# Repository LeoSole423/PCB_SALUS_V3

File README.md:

# PCB SALUS V3

PCB de control para el robot Ackermann SALUS. Esta revision se inspira en la
arquitectura de `Hoja-Base`, pero usa un ESP32-S3 y se mantiene como un diseno
independiente.

## Abrir el proyecto

En KiCad 10, abre `PCB_SALUS_v3.kicad_pro`. El esquema raiz contiene tres
hojas jerarquicas activas: `ESP32`, `SENSORES` y `ALIMENTACION`.

El diseño actual corresponde a `fabricacion/actual/JLCPCB_2026-10-15_SALUS_v3_D9_DNP/`.
Incluye cuatro agujeros M3 NPTH, contorno redondeado y R4 de 120 ohm montada
como terminacion RS-485. El sufijo R4 identifica esa resistencia. Las fuentes
en `origen/` coinciden con los archivos de trabajo al registrar este paquete.

Los informes archivados del 20 de agosto registran cero conexiones sin rutear
y cero errores DRC/ERC, con avisos e ignorados documentados. Esto no sustituye
la validacion electrica ni las pruebas de banco. Antes de pedir, seguir
`README-pedido.txt` y revisar el montaje en el visor JLCPCB.

`JLCPCB_2026-08-20_SALUS_v3/` conserva la exportacion anterior del mismo dia,
sin R4 montada; los paquetes de julio y del 12 de agosto son historicos.

## Organización

- [Mapa del repositorio](docs/09_ORGANIZACION_REPOSITORIO.md).
- [Índice de fabricación](fabricacion/README.md): entrega actual, históricas y cotizaciones.
- [Archivo histórico](archivo/README.md): respaldos, v2 y exportaciones antiguas.
- `referencias/jlcpcb/`: plantillas XLSX del proveedor.

## Arquitectura actual

- `U8`: ESP32-S3-WROOM-1-N8R2.
- `U1`: LDO AMS1117CD-3.3; J5 alimenta `5V_SYS` mediante D7; D9 se conserva como DNP y USB J16 no alimenta la lógica.
- `JP1` cerrado alimenta `+3.3V` desde el LDO; `JP2` abierto permite una
  fuente alternativa por J20 con selección de puentes apropiada.
- J16 es USB nativo; J1 es debug UART0, J3/J21 son RS-485 mediante U2.
- BMI088, I2C, interfaz BTS7960, siete salidas de relé, Hall, finales,
  acelerador y PPM. Receptor RC previsto: FlySky FS-iA6B.
- J19 recibe 7 V externos para J17/J18; no hay conversión de potencia de tracción.

La [revisión completa del 15/10/2026](docs/reviews/2026-10-15/REVISION_COMPLETA.md)
registra los límites actuales: no hay aprobación incondicional para fabricar
ni integrar. Resolver especialmente el rango del LM358, alimentación e interfaces.
La documentación histórica que menciona U9 buck o U3 CP2102N describe etapas anteriores.

## Documentacion

- [Contexto del proyecto](docs/00_CONTEXTO_PROYECTO.md)
- [Estructura del esquematico y librerias](docs/01_ESTRUCTURA_ESQUEMATICO_Y_LIBRERIAS.md)
- [Validacion y pruebas](docs/02_VALIDACION_Y_PRUEBAS.md)
- [Revision BOM y huellas JLCPCB](docs/03_REVISION_BOM_JLCPCB.md)
- [Puente H BTS7960](docs/04_PUENTE_H_BTS7960.md)
- [Mapa de submodulos y pinout](docs/05_MAPA_DE_SUBMODULOS_Y_PINOUT.md)
- [Revision V3](docs/06_REVISION_V3_2026-07-15.md)
- [Generacion CPL auditable KiCad → JLCPCB](docs/07_CPL_AUDITABLE_KICAD_JLCPCB.md)
- [Validacion del filtro PWM del acelerador](docs/08_VALIDACION_FILTRO_ACELERADOR_PWM.md)

## CPL para JLCPCB

Para toda exportación futura de montaje usar exclusivamente
`tools/jlc_cpl.py` y el perfil versionado `config/jlcpcb-cpl.json`. La guía
incluye el flujo reproducible para agentes, auditoría de centroides y
calibración desde el visor de JLCPCB. No editar rotaciones o posiciones
directamente en un CSV.

## Decisiones de integración

El [registro del 15/10/2026](docs/reviews/2026-10-15/DECISIONES_Y_PENDIENTES.md) distingue decisiones y cambios pendientes: conservar el lineal de 3.3 V, USB Serial/JTAG para la Jetson y no añadir detección VBUS. D9 ya está marcado DNP en esquema y PCB y excluido del montaje de la entrega actual. Sus pads/pistas permanecen; no montar ni puentear D9.

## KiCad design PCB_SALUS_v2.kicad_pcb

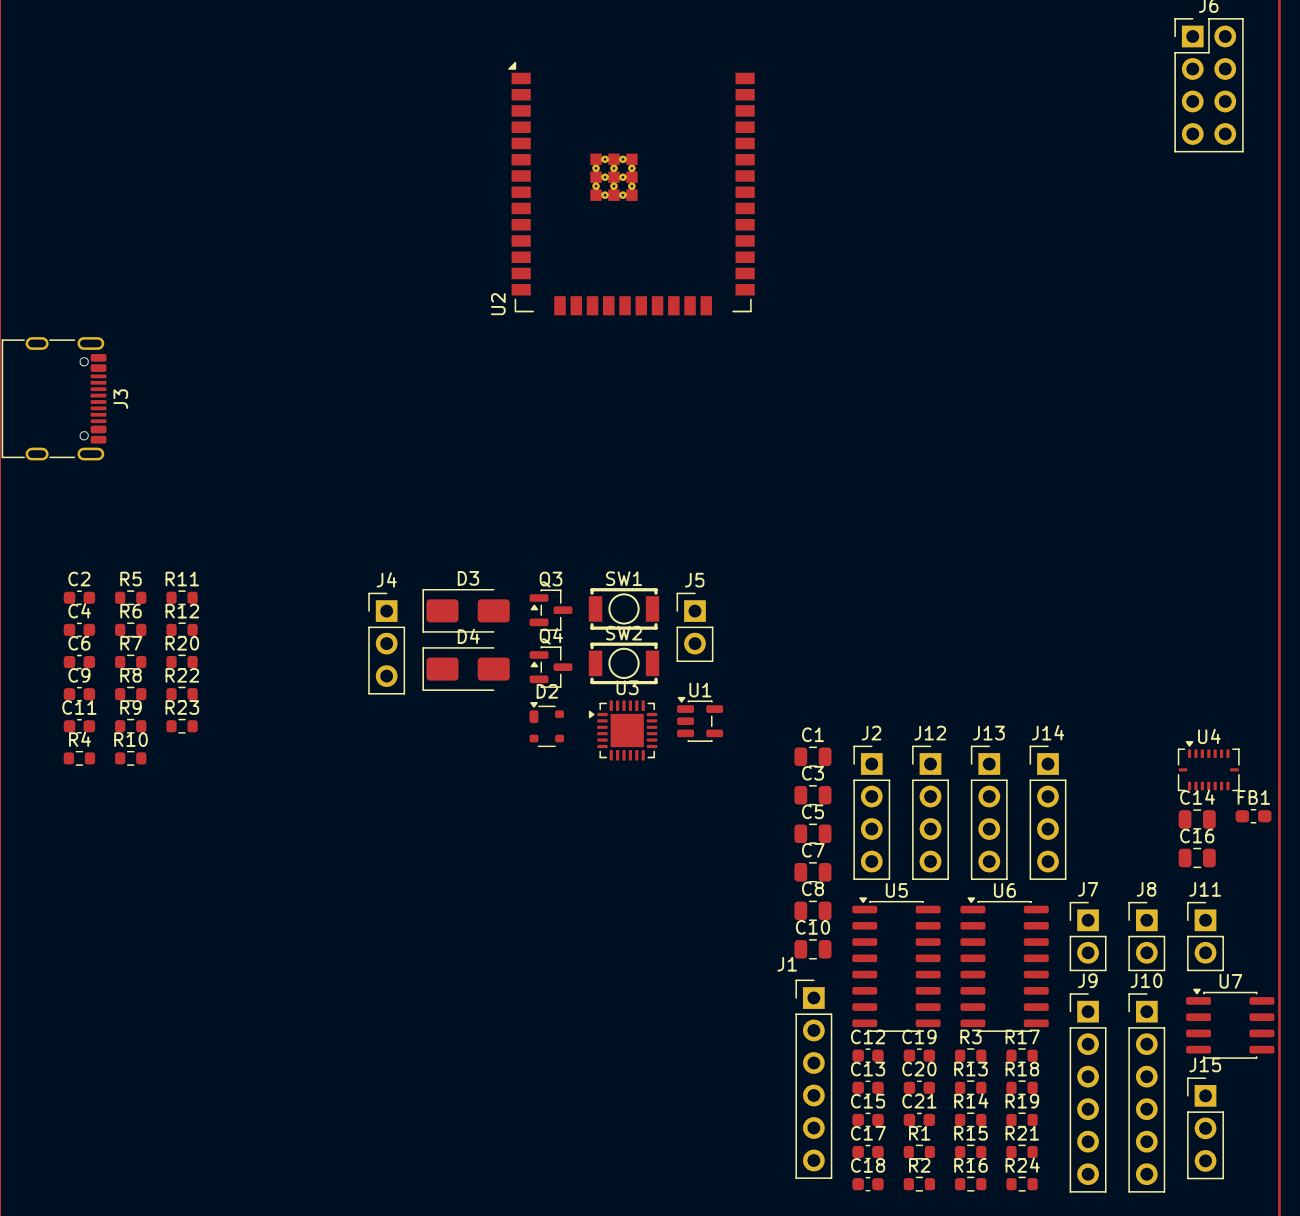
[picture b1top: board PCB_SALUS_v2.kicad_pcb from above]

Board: 2 copper layers, 75 parts (0 on the bottom side), 65 nets, no tracks yet.

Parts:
C1, C3, C5, C8: 10uF; C_0805_2012Metric
C2, C4, C6, C9, C11, C12, C13, C15, C17, C18, C19, C20, C21: 100nF; C_0603_1608Metric
C7, C10, C14, C16: 4.7uF; C_0805_2012Metric
D2: SP0503BAHTG; SOT-143
D3, D4: SS14; D_SMA
FB1: 600R@100MHz; L_0603_1608Metric_Pad1.05x0.95mm_HandSolder
J1: Header_THT_1x06_P2.54mm; PinHeader_1x06_P2.54mm_Vertical
J2, J12, J13, J14: Conn_01x04; PinHeader_1x04_P2.54mm_Vertical
J3: USB_C_Receptacle_USB2.0_16P; USB_C_Receptacle_G-Switch_GT-USB-7010ASV
J4: Header_THT_1x03_P2.54mm; PinHeader_1x03_P2.54mm_Vertical
J5, J7, J8, J11: Conn_01x02; PinHeader_1x02_P2.54mm_Vertical
J6: Conn_02x04_Odd_Even; PinHeader_2x04_P2.54mm_Vertical
J9, J10: Conn_01x06; PinHeader_1x06_P2.54mm_Vertical
J15: Conn_01x03; PinHeader_1x03_P2.54mm_Vertical
Q3, Q4: SS8050; SOT-23
R1, R8, R9, R13, R14, R15, R16, R20, R22, R23, R24: 10k; R_0603_1608Metric
R2, R3: R; R_0603_1608Metric
R4, R5: 5.1k; R_0603_1608Metric
R6: 22.1k; R_0603_1608Metric
R7: 47.5k; R_0603_1608Metric
R10, R11, R12, R17: 1k; R_0603_1608Metric
R18: 330; R_0603_1608Metric
R19: 47k; R_0603_1608Metric
R21: 4.7k; R_0603_1608Metric
SW1, SW2: Boton_Simple
U1: TLV75733PDBV; SOT-23-5
U2: ESP32-WROOM-32E
U3: CP2102N-A02-GQFN24; QFN-24-1EP_4x4mm_P0.5mm_EP2.6x2.6mm
U4: BMI088; Bosch_LGA-16_4.5x3mm_P0.5mm_LayoutBorder7x1y_ClockwisePinNu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
U5: 74HC595; SOIC-16_3.9x9.9mm_P1.27mm
U6: ULN2003A; SOIC-16_3.9x9.9mm_P1.27mm
U7: LM358; SOIC-8_3.9x4.9mm_P1.27mm

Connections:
5V_SYS: C3.1, C4.1, D3.1 (K), D4.1 (K), U1.1 (IN), U1.3 (EN)
+3.3V: C1.1, C2.1, C5.1, C6.1, C15.2, C16.1, C19.1, FB1.2, J2.1, J12.2, J13.2, R2.1, R3.1, R15.2, R16.2, R22.2, R23.2, U1.5 (OUT), U2.2 (VDD), U5.16 (VCC)
+5V: C21.1, D3.2 (A), J1.2, J5.1, J6.2, J9.1, J10.1, J15.2, U7.8 (V+)
/ESP32/BOOT: J1.6, Q4.3 (C), R23.1, SW1.1, U2.25 (IO0)
/ESP32/DTR: Q4.2 (E), R8.1, U3.23 (~DTR)
/ESP32/RESET: C8.1, J1.5, Q3.3 (C), R22.1, SW2.1, U2.3 (EN)
/ESP32/RTS: Q3.2 (E), R9.1, U3.19 (~RTS)
/ESP32/U0RX: J1.4, U2.34 (RXD0/IO3), U3.21 (TXD)
/ESP32/U0TX: J1.3, U2.35 (TXD0/IO1), U3.20 (RXD)
/ESP32/U1_RX: J4.2, R11.1
/ESP32/U1_TX: J4.1, R12.1
/ESP32/USB_DM: D2.4 (K), J3.A7 (D-), J3.B7 (D-), U3.4 (D-)
/ESP32/USB_DP: D2.3 (K), J3.A6 (D+), J3.B6 (D+), U3.3 (D+)
/SENSORES/IMU_3.3: C12.2, C13.1, C14.2, FB1.1, R13.1, R14.1, U4.3 (VDD), U4.11 (VDDIO)
/SENSORES/THROTTLE_OUT: J11.1, R18.2, R19.1
CP2102_3V3: C10.2, C11.1, R10.1, U3.5 (VIO), U3.6 (VDD)
CS_ACCEL: R14.2, U2.26 (IO4), U4.14 (~CSB1)
CS_GIRO: R13.2, U2.11 (IO26), U4.5 (~CSB2)
DAC: R17.1, U2.10 (IO25)
DR_ACCEL: U2.6 (IO34), U4.16 (INT1)
DR_GIRO: U2.7 (IO35), U4.12 (INT3)
FC_LEFT: C17.1, J7.1, R2.2, U2.4 (SENSOR_VP)
FC_RIGHT: C18.1, J8.1, R3.2, U2.5 (SENSOR_VN)
GND: C1.2, C2.2, C3.2, C4.2, C5.2, C6.2, C7.1, C8.2, C9.2, C10.1, C11.2, C12.1, C13.2, C14.1, C15.1, C16.2, C17.2, C18.2, C19.2, C20.2, C21.2, D2.1 (A), J1.1, J2.2, J3.A1 (GND), J3.A12 (GND), J3.B1 (GND), J3.B12 (GND), J3.SH (SHIELD), J4.3, J5.2, J6.1, J7.2, J8.2, J9.6, J10.6, J11.2, J12.1, J13.1, J14.4, J15.1, R1.2, R4.2, R5.2, R7.2, R19.2, R20.1, R24.2, SW1.2, SW2.2, U1.2 (GND), U2.1 (GND), U2.15 (GND), U2.38 (GND), U2.39 (GND), U3.2 (GND), U3.25 (GND), U4.2 (GNDA), U4.4 (GNDA), U4.6 (GNDIO), U4.7 (PS), U5.8 (GND), U6.8 (GND), U7.4 (V-), U7.5 (+)
HALL_A: J14.1, U2.29 (IO5)
HALL_B: J14.2, U2.16 (IO13)
HALL_C: J14.3, U2.23 (IO15)
HBRIDGE_EN: J6.5, J6.6, R1.1, U5.6 (QG)
I2C_SCL: J2.4, J12.4, J13.4, U2.36 (IO22)
I2C_SDA: J2.3, J12.3, J13.3, U2.33 (IO21)
L_PWM: J6.7, U2.9 (IO33)
unnamed: J3.A5 (CC1), R4.1
unnamed: J3.B5 (CC2), R5.1
unnamed: J9.2, U6.16 (O1)
unnamed: J9.3, U6.15 (O2)
unnamed: J9.4, U6.14 (O3)
unnamed: J9.5, U6.13 (O4)
unnamed: J10.2, U6.12 (O5)
unnamed: J10.3, U6.11 (O6)
unnamed: J10.4, U6.10 (O7)
unnamed: J15.3, R21.1, R24.1
unnamed: Q3.1 (B), R8.2
unnamed: Q4.1 (B), R9.2
unnamed: R11.2, U2.27 (IO16)
unnamed: R12.2, U2.28 (IO17)
unnamed: R6.2, R7.1, U3.8 (VBUS)
unnamed: R10.2, U3.9 (~RST)
unnamed: U5.15 (QA), U6.1 (I1)
unnamed: U5.1 (QB), U6.2 (I2)
unnamed: U5.2 (QC), U6.3 (I3)
unnamed: U5.3 (QD), U6.4 (I4)
unnamed: U5.4 (QE), U6.5 (I5)
unnamed: U5.5 (QF), U6.6 (I6)
unnamed: R15.1, U5.10 (~SRCLR)
unnamed: C20.1, R17.2, U7.3 (+)
unnamed: R18.1, U7.1, U7.2 (-)
unnamed: U7.6 (-), U7.7
RELAY_LATCH: R20.2, U2.14 (IO12), U5.12 (RCLK)
RELAY_OE: R16.1, U2.13 (IO14), U5.13 (~OE)
RF_PPM: R21.2, U2.8 (IO32)
R_PWM: J6.8, U2.12 (IO27)
SPI_CLOCK: U2.30 (IO18), U4.8 (SCK/SCL), U5.11 (SRCLK)
SPI_MISO: U2.31 (IO19), U4.10 (SDO2), U4.15 (SDO1)
SPI_MOSI: U2.37 (IO23), U4.9 (SDI/SDA), U5.14 (SER)
USB_VBUS: C7.2, C9.1, D2.2 (K), D4.2 (A), J3.A4 (VBUS), J3.A9 (VBUS), J3.B4 (VBUS), J3.B9 (VBUS), R6.1, U3.7 (VREGIN)

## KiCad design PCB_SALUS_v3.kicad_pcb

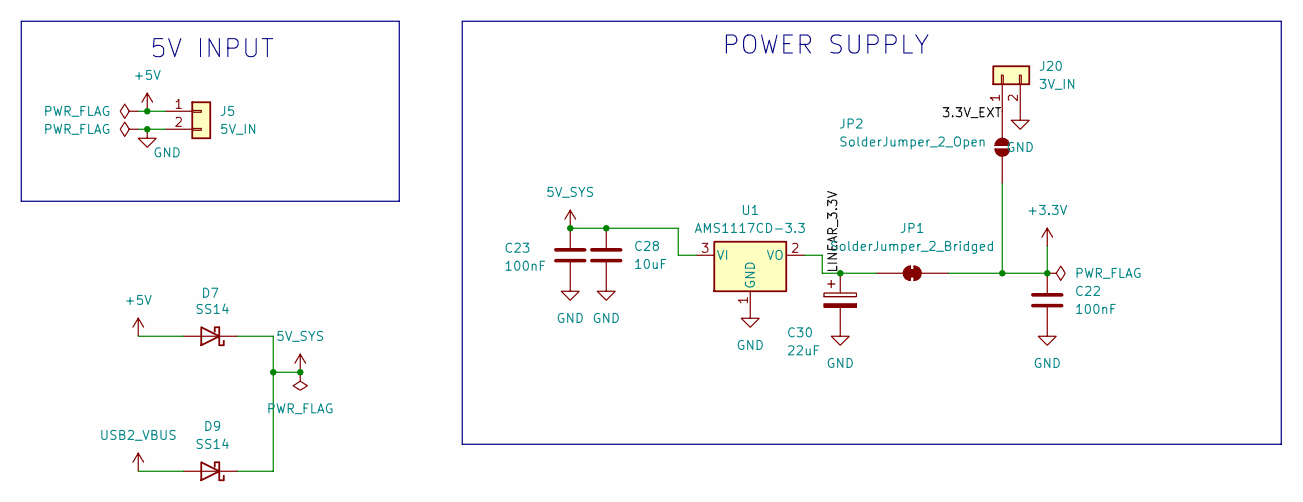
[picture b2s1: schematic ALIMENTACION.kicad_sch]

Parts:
C22, C23: 100nF; C_0603_1608Metric; Manufacturer Part CL10B104KA8NNNC; LCSC PN C1590
C28: 10uF; C_0805_2012Metric; Manufacturer Part CL21A106KPFNNNE; LCSC PN C17024
C30: 22uF; CP_EIA-3528-21_Kemet-B; Manufacturer Part T491B226K010AT; LCSC PN C117030
D7, D9: SS14; D_SMA; Manufacturer Part SS14; LCSC PN C2480
J5: 5V_IN; PinHeader_1x02_P2.54mm_Vertical; MPN Header manual THT 1x02 P2.54 mm
J20: 3V_IN; PinHeader_1x02_P2.54mm_Vertical
JP1: SolderJumper_2_Bridged; SolderJumper-2_P1.3mm_Bridged_RoundedPad1.0x1.5mm
JP2: SolderJumper_2_Open; SolderJumper-2_P1.3mm_Open_RoundedPad1.0x1.5mm
U1: AMS1117CD-3.3; TO-252-3_TabPin2; MPN AMS1117CD-3.3; LCSC PN C841796

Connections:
5V_SYS: C23.1, C28.1, D7.1 (K), D9.1 (K), U1.3 (VI)
+3.3V: C22.1, JP1.2 (B), JP2.2 (B); also elsewhere on the board
+5V: D7.2 (A), J5.1; also elsewhere on the board
/ALIMENTACION/3.3V_EXT: J20.1, JP2.1 (A)
/ALIMENTACION/LINEAR_3.3V: C30.1, JP1.1 (A), U1.2 (VO)
GND: C22.2, C23.2, C28.2, C30.2, J5.2, J20.2, U1.1 (GND); also elsewhere on the board
USB2_VBUS: D9.2 (A); also elsewhere on the board

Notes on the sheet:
POWER SUPPLY
5V INPUT

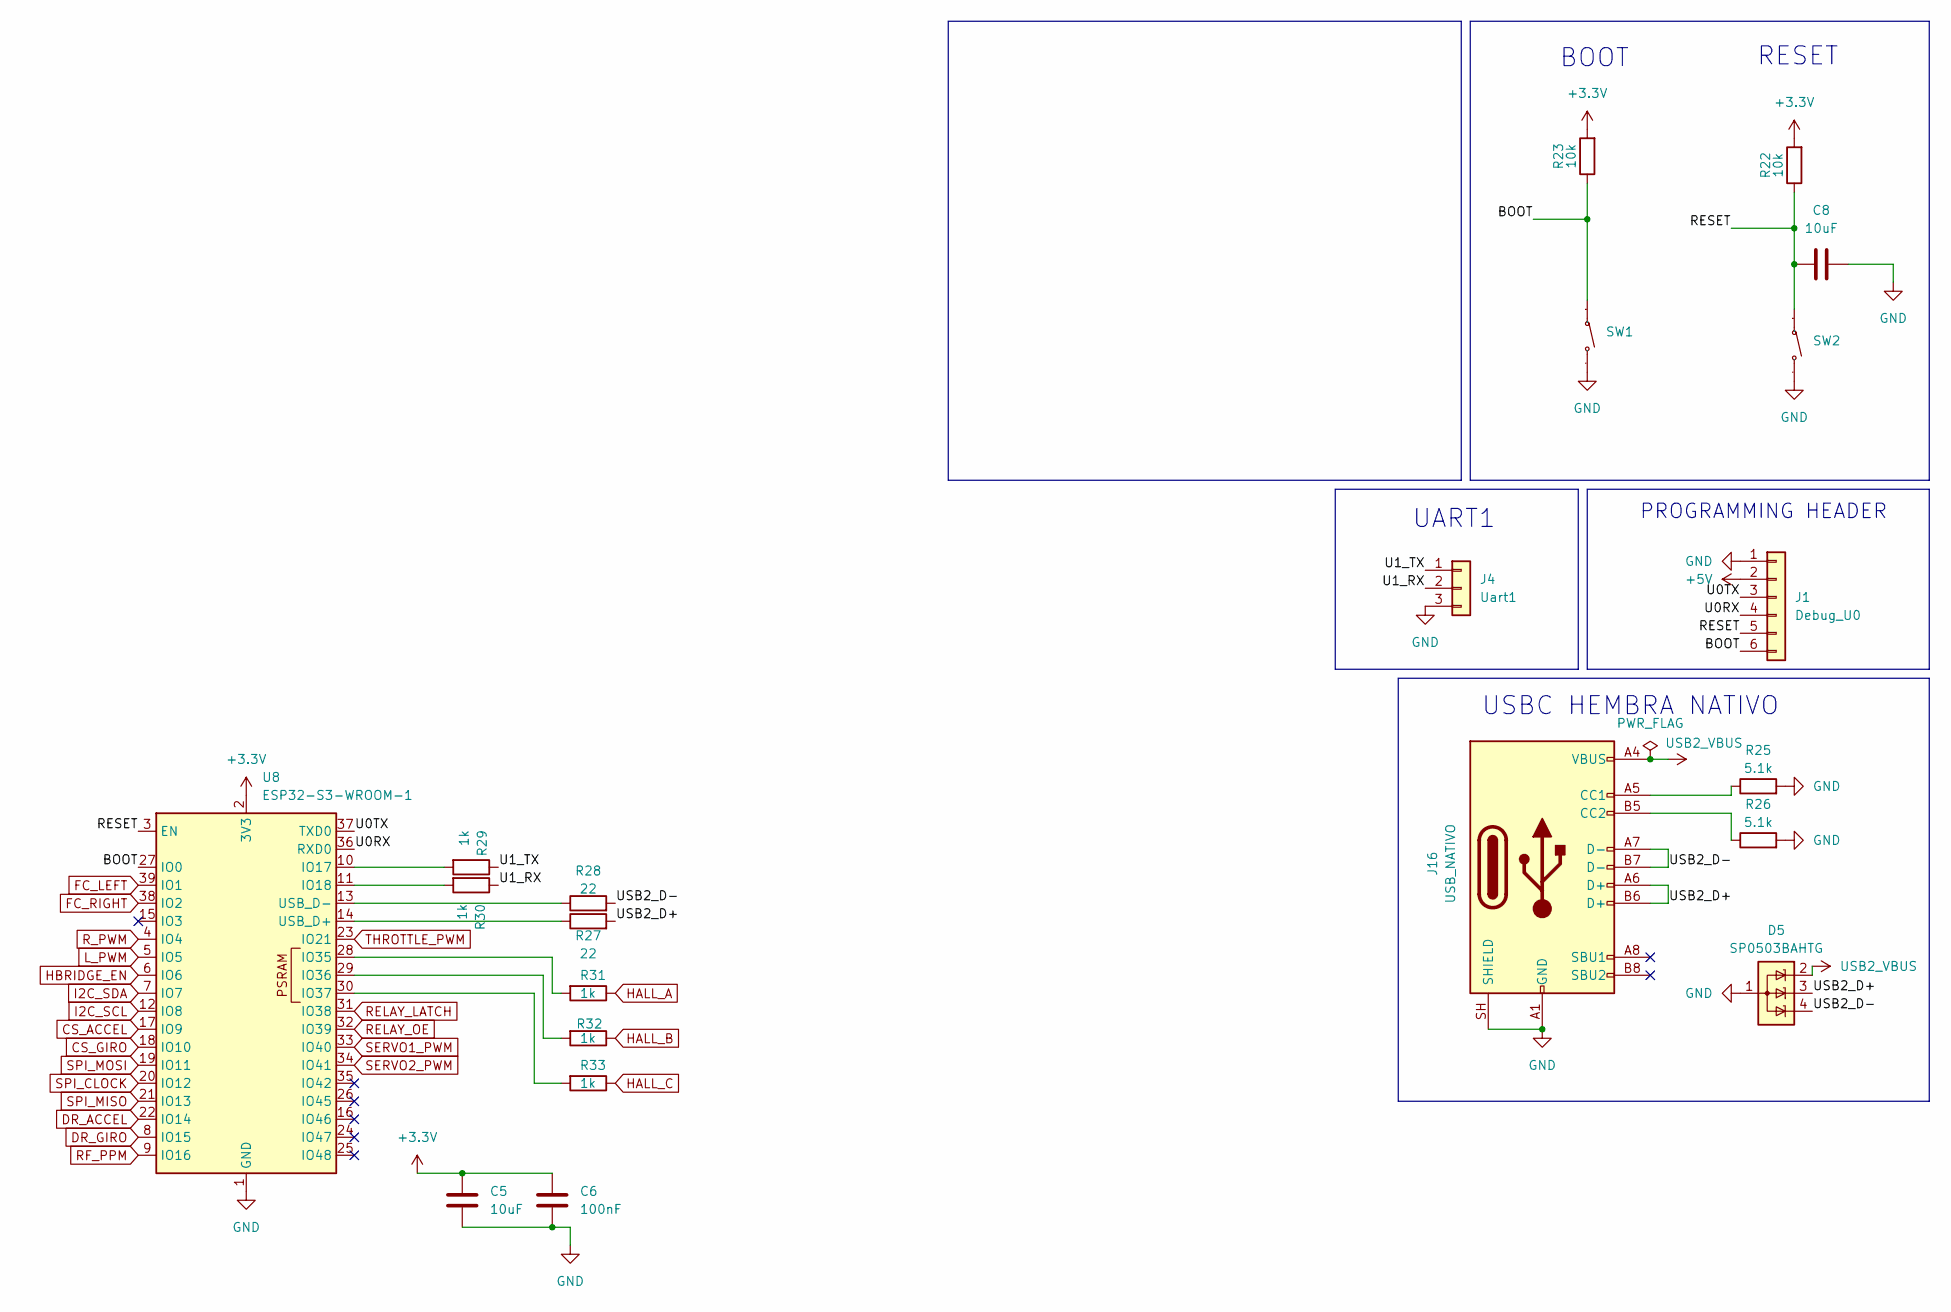
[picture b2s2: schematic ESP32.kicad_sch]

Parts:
C5, C8: 10uF; C_0805_2012Metric; Manufacturer Part CL21A106KPFNNNE; LCSC PN C17024
C6: 100nF; C_0603_1608Metric; Manufacturer Part CL10B104KA8NNNC; LCSC PN C1590
D5: SP0503BAHTG; SOT-143; Manufacturer Part SP0503BAHTG; LCSC PN C3040626
J1: Debug_U0; PinHeader_1x06_P2.54mm_Vertical; Manufacturer Part Header generico THT 1x06, P2.54 mm, ver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
J4: Uart1; PinHeader_1x03_P2.54mm_Vertical; Manufacturer Part Header generico THT 1x03, P2.54 mm, ver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
J16: USB_NATIVO; USB_C_Receptacle_G-Switch_GT-USB-7010ASV; Manufacturer Part GT-USB-7010ASV; LCSC PN C2988369
R22, R23: 10k; R_0603_1608Metric; Manufacturer Part 0603WAF1002T5E; LCSC PN C25804
R25, R26: 5.1k; R_0603_1608Metric; Manufacturer Part 0603WAF5101T5E; LCSC PN C23186
R27, R28: 22; R_0603_1608Metric; MPN 0603WAF220JT5E; LCSC PN C23345
R29, R30, R31, R32, R33: 1k; R_0603_1608Metric; Manufacturer Part 0603WAF1001T5E; LCSC PN C21190
SW1, SW2: Boton_Simple; Manufacturer Part TS1201-TZ25HAM; LCSC Part Name 立贴 轻触开关
U8: ESP32-S3-WROOM-1; Manufacturer Part ESP32-S3-WROOM-1-N8R2; LCSC PN C2913204

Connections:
+3.3V: C5.1, C6.1, R22.2, R23.2, U8.2 (3V3); also elsewhere on the board
+5V: J1.2; also elsewhere on the board
/ESP32/BOOT: J1.6, R23.1, SW1.1, U8.27 (IO0)
/ESP32/IO3: U8.15 (IO3); also elsewhere on the board
/ESP32/IO45: U8.26 (IO45); also elsewhere on the board
/ESP32/IO46: U8.16 (IO46); also elsewhere on the board
/ESP32/IO47: U8.24 (IO47); also elsewhere on the board
/ESP32/IO48: U8.25 (IO48); also elsewhere on the board
/ESP32/RESET: C8.1, J1.5, R22.1, SW2.1, U8.3 (EN)
/ESP32/U0RX: J1.4, U8.36 (RXD0)
/ESP32/U0TX: J1.3, U8.37 (TXD0)
/ESP32/U1_RX: J4.2, R30.1; also elsewhere on the board
/ESP32/U1_TX: J4.1, R29.1; also elsewhere on the board
/ESP32/USB2_D+: D5.3 (K), J16.A6 (D+), J16.B6 (D+), R27.2
/ESP32/USB2_D-: D5.4 (K), J16.A7 (D-), J16.B7 (D-), R28.2
CS_ACCEL: U8.17 (IO9); also elsewhere on the board
CS_GIRO: U8.18 (IO10); also elsewhere on the board
DR_ACCEL: U8.22 (IO14); also elsewhere on the board
DR_GIRO: U8.8 (IO15); also elsewhere on the board
FC_LEFT: U8.39 (IO1); also elsewhere on the board
FC_RIGHT: U8.38 (IO2); also elsewhere on the board
GND: C5.2, C6.2, C8.2, D5.1 (A), J1.1, J4.3, J16.A1 (GND), J16.A12 (GND), J16.B1 (GND), J16.B12 (GND), J16.SH (SHIELD), R25.2, R26.2, SW1.2, SW2.2, U8.1 (GND), U8.40 (GND), U8.41 (GND); also elsewhere on the board
HALL_A: R31.1; also elsewhere on the board
HALL_B: R32.1; also elsewhere on the board
HALL_C: R33.1; also elsewhere on the board
HBRIDGE_EN: U8.6 (IO6); also elsewhere on the board
I2C_SCL: U8.12 (IO8); also elsewhere on the board
I2C_SDA: U8.7 (IO7); also elsewhere on the board
L_PWM: U8.5 (IO5); also elsewhere on the board
unnamed: J16.A5 (CC1), R25.1
unnamed: J16.B5 (CC2), R26.1
unnamed: R29.2, U8.10 (IO17)
unnamed: R30.2, U8.11 (IO18)
unnamed: R31.2, U8.28 (IO35)
unnamed: R32.2, U8.29 (IO36)
unnamed: R33.2, U8.30 (IO37)
unnamed: R27.1, U8.14 (USB_D+)
unnamed: R28.1, U8.13 (USB_D-)
RELAY_LATCH: U8.31 (IO38); also elsewhere on the board
RELAY_OE: U8.32 (IO39); also elsewhere on the board
RS485_DIR: U8.35 (IO42); also elsewhere on the board
R_PWM: U8.4 (IO4); also elsewhere on the board
SERVO1_PWM: U8.33 (IO40); also elsewhere on the board
SERVO2_PWM: U8.34 (IO41); also elsewhere on the board
SPI_CLOCK: U8.20 (IO12); also elsewhere on the board
SPI_MISO: U8.21 (IO13); also elsewhere on the board
SPI_MOSI: U8.19 (IO11); also elsewhere on the board
THROTTLE_PWM: U8.23 (IO21); also elsewhere on the board
USB2_VBUS: D5.2 (K), J16.A4 (VBUS), J16.A9 (VBUS), J16.B4 (VBUS), J16.B9 (VBUS); also elsewhere on the board

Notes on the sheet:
BOOT
UART1
USBC HEMBRA NATIVO
RESET
PROGRAMMING HEADER

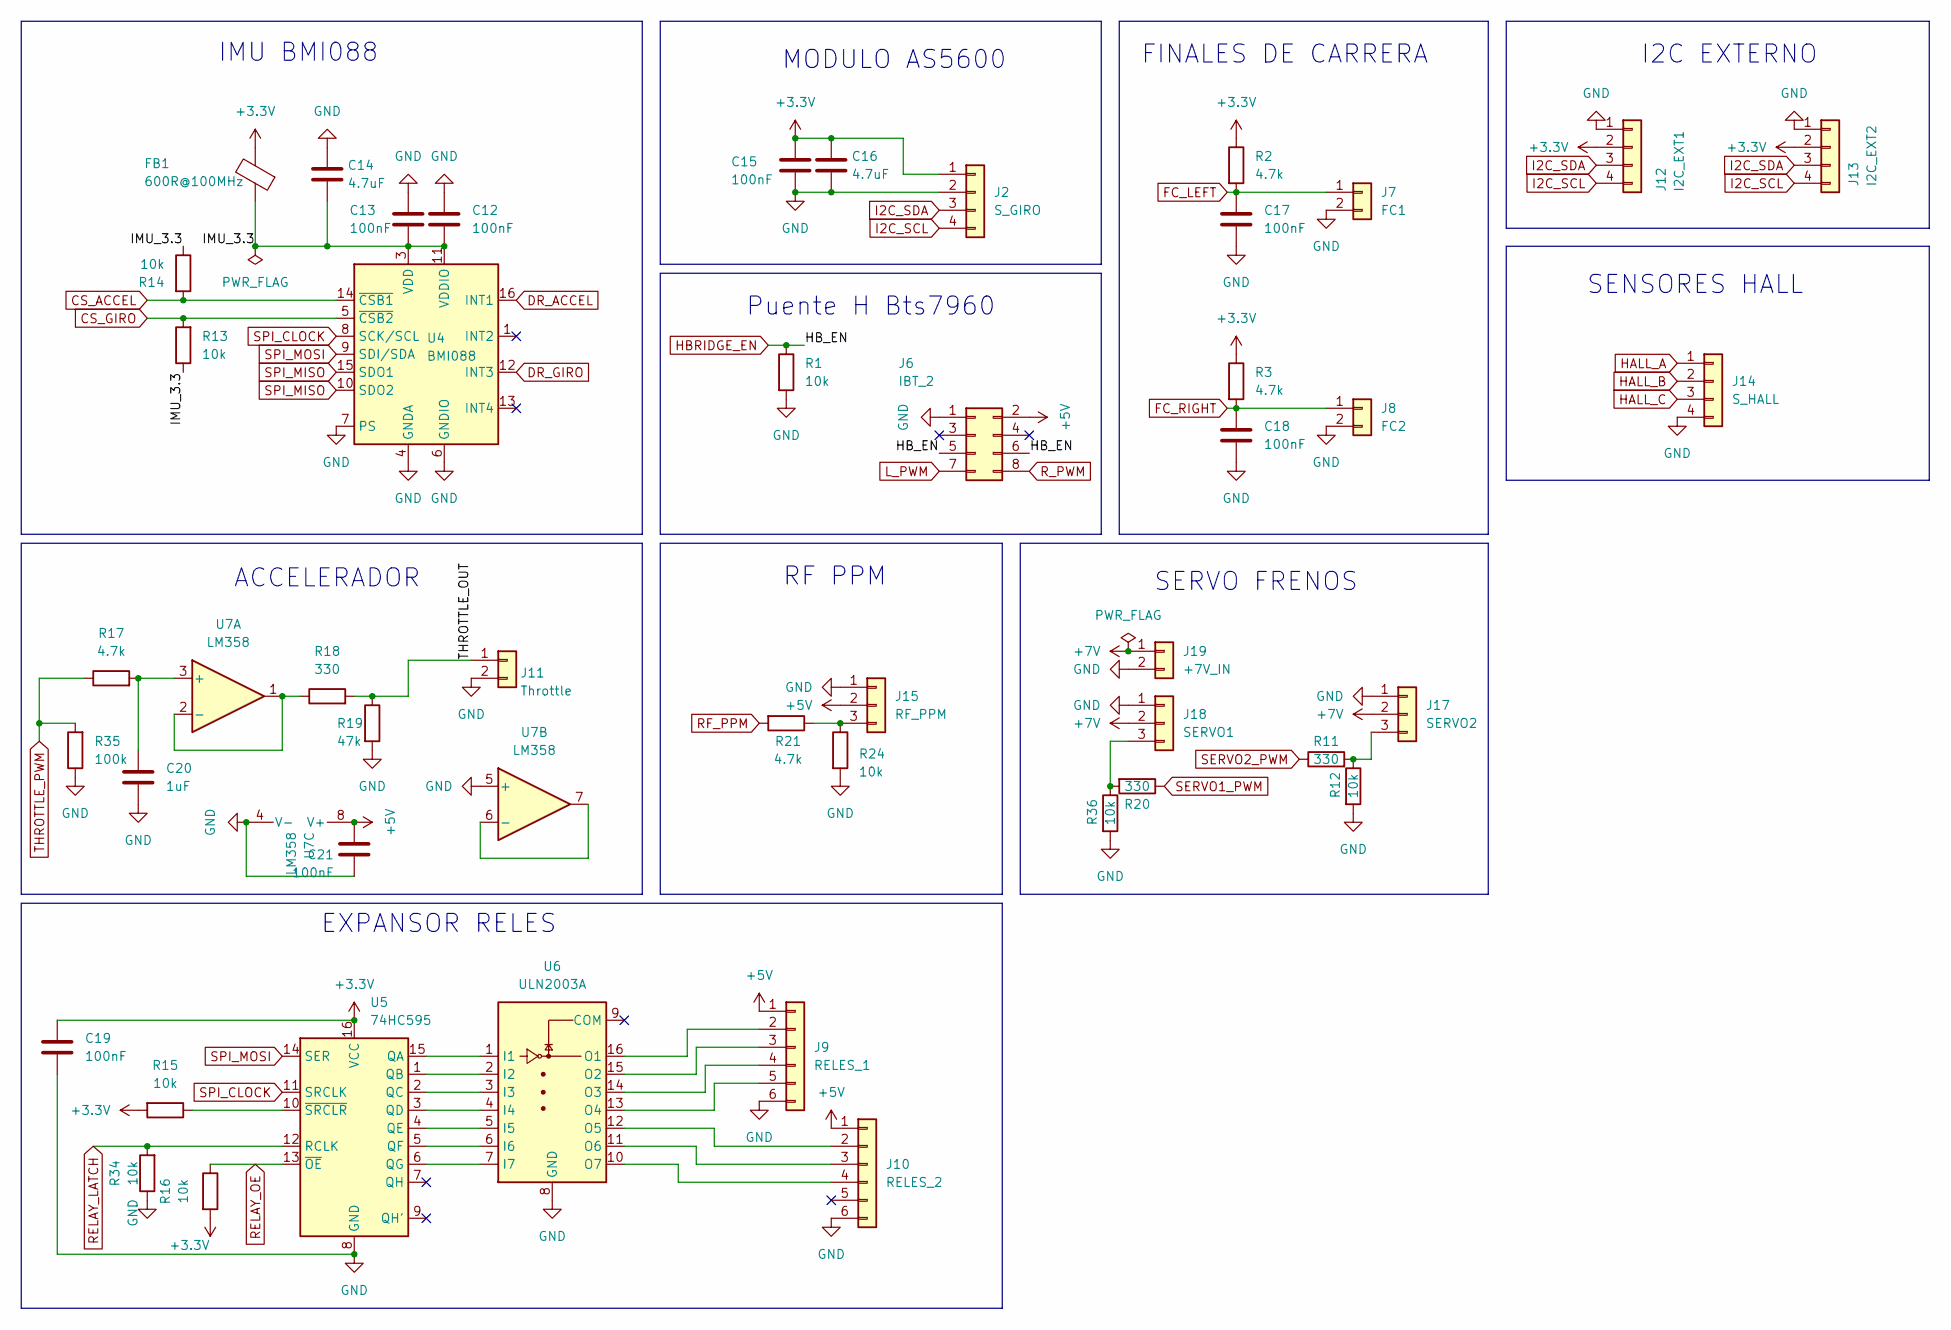
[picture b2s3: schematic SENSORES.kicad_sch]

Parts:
C12, C13, C15: 100nF; C_0603_1608Metric; Manufacturer Part CL10B104KA8NNNC; LCSC PN C1590
C14, C16: 4.7uF; C_0805_2012Metric; Manufacturer Part CC0805KKX5R6BB475; LCSC PN C107125
C17, C18, C19, C21: 100nF; C_0603_1608Metric; MPN CL10B104KA8NNNC; LCSC PN C1590
C20: 1uF; C_0603_1608Metric; MPN 0603B105K160CT; LCSC PN C108463
FB1: 600R@100MHz; L_0603_1608Metric_Pad1.05x0.95mm_HandSolder; Manufacturer Part GZ1608D601TF; LCSC PN C1002
J2: S_GIRO; PinHeader_1x04_P2.54mm_Vertical; MPN Header manual THT 1x04 P2.54 mm
J6: IBT_2; PinHeader_2x04_P2.54mm_Vertical; MPN Header manual THT 2x04 P2.54 mm
J7: FC1; PinHeader_1x02_P2.54mm_Vertical; MPN Header manual THT 1x02 P2.54 mm
J8: FC2; PinHeader_1x02_P2.54mm_Vertical; MPN Header manual THT 1x02 P2.54 mm
J9: RELES_1; PinHeader_1x06_P2.54mm_Vertical; MPN Header manual THT 1x06 P2.54 mm
J10: RELES_2; PinHeader_1x06_P2.54mm_Vertical; MPN Header manual THT 1x06 P2.54 mm
J11: Throttle; PinHeader_1x02_P2.54mm_Vertical; MPN Header manual THT 1x02 P2.54 mm
J12: I2C_EXT1; PinHeader_1x04_P2.54mm_Vertical; MPN Header manual THT 1x04 P2.54 mm
J13: I2C_EXT2; PinHeader_1x04_P2.54mm_Vertical; MPN Header manual THT 1x04 P2.54 mm
J14: S_HALL; PinHeader_1x04_P2.54mm_Vertical; MPN Header manual THT 1x04 P2.54 mm
J15: RF_PPM; PinHeader_1x03_P2.54mm_Vertical; MPN Header manual THT 1x03 P2.54 mm
J17: SERVO2; PinHeader_1x03_P2.54mm_Vertical; MPN Header manual THT 1x03 P2.54 mm
J18: SERVO1; PinHeader_1x03_P2.54mm_Vertical; MPN Header manual THT 1x03 P2.54 mm
J19: +7V_IN; PinHeader_1x02_P2.54mm_Vertical; MPN Header manual THT 1x02 P2.54 mm
R1, R12, R15, R16, R24, R34, R36: 10k; R_0603_1608Metric; MPN 0603WAF1002T5E; LCSC PN C25804
R2, R3, R17, R21: 4.7k; R_0603_1608Metric; MPN 0603WAF4701T5E; LCSC PN C23162
R11, R18, R20: 330; R_0603_1608Metric; MPN 0603WAF3300T5E; LCSC PN C23138
R13, R14: 10k; R_0603_1608Metric; Manufacturer Part 0603WAF1002T5E; LCSC PN C25804
R19: 47k; R_0603_1608Metric; MPN 0603WAF4702T5E; LCSC PN C25819
R35: 100k; R_0603_1608Metric; MPN 0603WAF1003T5E; LCSC PN C25803
U4: BMI088; Bosch_LGA-16_4.5x3mm_P0.5mm_LayoutBorder7x1y_ClockwisePinNu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; Manufacturer Part BMI088; LCSC PN C194919
U5: 74HC595; SOIC-16_3.9x9.9mm_P1.27mm; Manufacturer Part SN74HC595DR; LCSC PN C10092
U6: ULN2003A; SOIC-16_3.9x9.9mm_P1.27mm; Manufacturer Part ULN2003BDR; LCSC PN C157485
U7: LM358; SOIC-8_3.9x4.9mm_P1.27mm; Manufacturer Part LM358DR; LCSC PN C5423

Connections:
+3.3V: C15.2, C16.1, C19.1, FB1.2, J2.1, J12.2, J13.2, R2.1, R3.1, R15.2, R16.2, U5.16 (VCC); also elsewhere on the board
+5V: C21.1, J6.2, J9.1, J10.1, J15.2, U7.8 (V+); also elsewhere on the board
+7V: J17.2, J18.2, J19.1
/SENSORES/IMU_3.3: C12.2, C13.1, C14.2, FB1.1, R13.1, R14.1, U4.3 (VDD), U4.11 (VDDIO)
/SENSORES/THROTTLE_OUT: J11.1, R18.2, R19.1
CS_ACCEL: R14.2, U4.14 (~CSB1); also elsewhere on the board
CS_GIRO: R13.2, U4.5 (~CSB2); also elsewhere on the board
DR_ACCEL: U4.16 (INT1); also elsewhere on the board
DR_GIRO: U4.12 (INT3); also elsewhere on the board
FC_LEFT: C17.1, J7.1, R2.2; also elsewhere on the board
FC_RIGHT: C18.1, J8.1, R3.2; also elsewhere on the board
GND: C12.1, C13.2, C14.1, C15.1, C16.2, C17.2, C18.2, C19.2, C20.2, C21.2, J2.2, J6.1, J7.2, J8.2, J9.6, J10.6, J11.2, J12.1, J13.1, J14.4, J15.1, J17.1, J18.1, J19.2, R1.2, R12.2, R19.2, R24.2, R34.1, R35.1, R36.2, U4.2 (GNDA), U4.4 (GNDA), U4.6 (GNDIO), U4.7 (PS), U5.8 (GND), U6.8 (GND), U7.4 (V-), U7.5 (+); also elsewhere on the board
HALL_A: J14.1; also elsewhere on the board
HALL_B: J14.2; also elsewhere on the board
HALL_C: J14.3; also elsewhere on the board
HBRIDGE_EN: J6.5, J6.6, R1.1; also elsewhere on the board
I2C_SCL: J2.4, J12.4, J13.4; also elsewhere on the board
I2C_SDA: J2.3, J12.3, J13.3; also elsewhere on the board
L_PWM: J6.7; also elsewhere on the board
unnamed: J9.2, U6.16 (O1)
unnamed: J9.3, U6.15 (O2)
unnamed: J9.4, U6.14 (O3)
unnamed: J9.5, U6.13 (O4)
unnamed: J10.2, U6.12 (O5)
unnamed: J10.3, U6.11 (O6)
unnamed: J10.4, U6.10 (O7)
unnamed: J17.3, R11.2, R12.1
unnamed: J18.3, R20.2, R36.1
unnamed: U5.15 (QA), U6.1 (I1)
unnamed: U5.1 (QB), U6.2 (I2)
unnamed: U5.2 (QC), U6.3 (I3)
unnamed: U5.3 (QD), U6.4 (I4)
unnamed: U5.4 (QE), U6.5 (I5)
unnamed: U5.5 (QF), U6.6 (I6)
unnamed: U5.6 (QG), U6.7 (I7)
unnamed: R15.1, U5.10 (~SRCLR)
unnamed: C20.1, R17.2, U7.3 (+)
unnamed: R18.1, U7.1, U7.2 (-)
unnamed: U7.6 (-), U7.7
RELAY_LATCH: R34.2, U5.12 (RCLK); also elsewhere on the board
RELAY_OE: R16.1, U5.13 (~OE); also elsewhere on the board
R_PWM: J6.8; also elsewhere on the board
SERVO1_PWM: R20.1; also elsewhere on the board
SERVO2_PWM: R11.1; also elsewhere on the board
SPI_CLOCK: U4.8 (SCK/SCL), U5.11 (SRCLK); also elsewhere on the board
SPI_MISO: U4.10 (SDO2), U4.15 (SDO1); also elsewhere on the board
SPI_MOSI: U4.9 (SDI/SDA), U5.14 (SER); also elsewhere on the board
THROTTLE_PWM: R17.1, R35.2; also elsewhere on the board

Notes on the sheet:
MODULO AS5600
Puente H Bts7960
EXPANSOR RELES
FINALES DE CARRERA
ACCELERADOR
SENSORES HALL
RF PPM
IMU BMI088
I2C EXTERNO
SERVO FRENOS

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
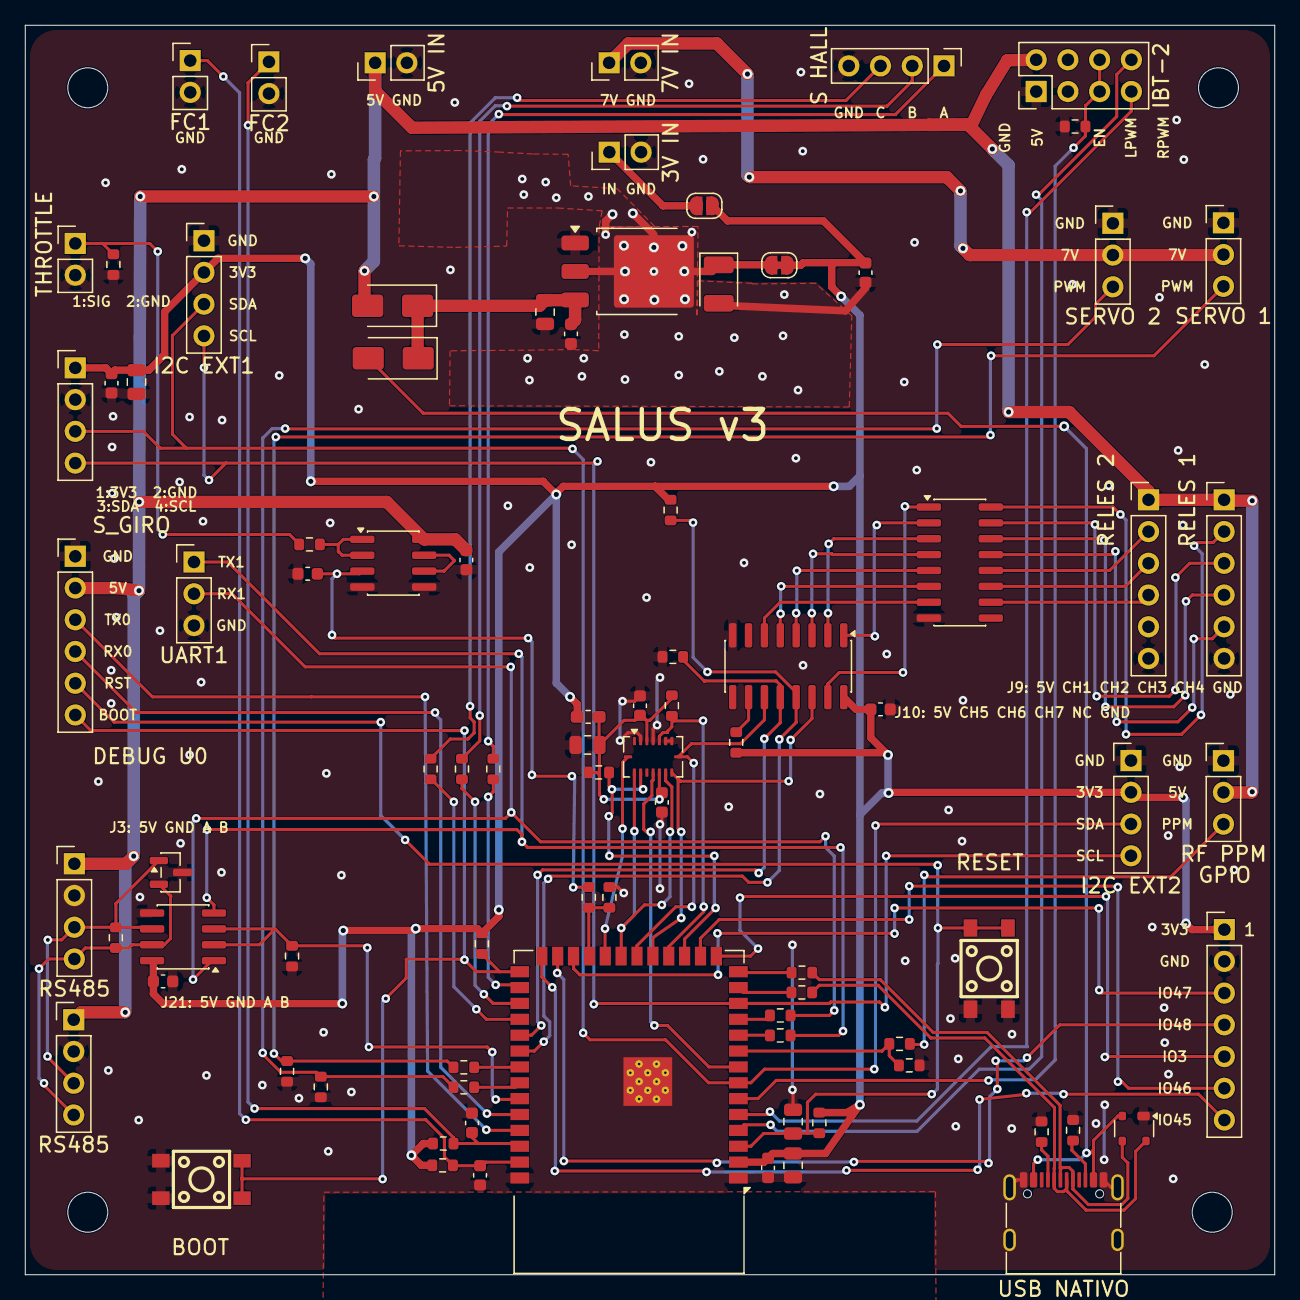
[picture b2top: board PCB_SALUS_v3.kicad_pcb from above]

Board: 2 copper layers, 100.0 x 100.0 mm, 91 parts (0 on the bottom side), 79 nets.

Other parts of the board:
C7: 100nF; C_0603_1608Metric
D1: SM712-02HTG; SOT-23
H1, H2, H3, H4: MountingHole_3.2mm_M3
J3, J21: RS485; PinHeader_1x04_P2.54mm_Vertical
J22: GPIOS_AUX; PinHeader_1x07_P2.54mm_Vertical
R4: 120; R_0603_1608Metric
R37: 10k; R_0603_1608Metric
U2: SP3485EN; SOIC-8_3.9x4.9mm_P1.27mm

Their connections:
+3.3V: C7.1, J22.1, U2.8 (VCC); also elsewhere on the board
+5V: J3.1, J21.1; also elsewhere on the board
/ESP32/IO3: J22.5; also elsewhere on the board
/ESP32/IO45: J22.7; also elsewhere on the board
/ESP32/IO46: J22.6; also elsewhere on the board
/ESP32/IO47: J22.3; also elsewhere on the board
/ESP32/IO48: J22.4; also elsewhere on the board
/ESP32/RS485_A: D1.1 (A1), J3.3, J21.3, R4.1, U2.6 (A)
/ESP32/RS485_B: D1.2 (A2), J3.4, J21.4, R4.2, U2.7 (B)
/ESP32/U1_RX: U2.1 (RO); also elsewhere on the board
/ESP32/U1_TX: U2.4 (DI); also elsewhere on the board
GND: C7.2, D1.3 (common), J3.2, J21.2, J22.2, R37.1, U2.5 (GND); also elsewhere on the board
RS485_DIR: R37.2, U2.2 (~RE), U2.3 (DE); also elsewhere on the board

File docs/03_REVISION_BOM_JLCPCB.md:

# Revision de BOM y huellas para JLCPCB

Fecha de revision: 2026-07-15.

## Alcance

Se revisaron `ESP32.kicad_sch`, `SENSORES.kicad_sch` y
`ALIMENTACION.kicad_sch`. Todos los SMD con valor definido tienen huella, MPN,
fabricante y `LCSC PN`. La excepcion es `R2/R3`: su valor sigue siendo `R`, por
lo cual quedan sin pieza de compra y no se deben montar.

Los stocks son una fotografia del 2026-07-15. Confirmar disponibilidad, precio,
Basic/Extended y elegibilidad Standard PCBA al preparar el pedido final.

## Piezas criticas

| Referencias | MPN / LCSC PN | Huella | Categoria JLC | Stock observado | Decision |
|---|---|---|---|---:|---|
| U8 | ESP32-S3-WROOM-1-N8R2 / C2913204 | RF_Module:ESP32-S3-WROOM-1 | Extended, Standard | 17,776 | Keep-out de antena obligatorio. |
| U9 | AP63203WU-7 / C780769 | TSOT-23-6 | Extended | 615 | Buck fijo de 3.3 V. |
| L2 | FXL0530-4R7-M / C177246 | L_Changjiang_FXL0530 | Extended | 150,986 | 4.7 uH, 4.5 A nominal, 5 A Isat. |
| C28 | CL21A106KPFNNNE / C17024 | 0805 | Extended | 1,868,129 | 10 uF para entrada del buck. |
| C30,C31 | CL21A226MAQNNNE / C45783 | 0805 | Extended | 5,389,915 | 22 uF; reemplaza MPN erroneo de 10 uF. |
| U3 | CP2102N-A02-GQFN24R / C969151 | QFN-24-EP 4x4 | Extended | 5,744 | USB-UART y pad expuesto a GND. |
| U4 | BMI088 / C194919 | Bosch LGA-16 4.5x3 | Extended, Standard | 2,378 | Verificar orientacion, desacople y placement. |
| J3,J16 | GT-USB-7010ASV / C2988369 | USB-C G-Switch | Extended | 32,723 | Un conector UART0 y uno USB nativo. |
| D2,D5 | SP0503BAHTG / C3040626 | SOT-143 | Extended | 28,729 | TVS USB, colocar junto al conector correspondiente. |

## Pasivos consolidados

| Valor | MPN / LCSC PN | Huella | Referencias de esta revision |
|---|---|---|---|
| 100 nF | CL10B104KA8NNNC / C1590 | 0603 | C6,C9,C11-C13,C15,C17-C19,C21-C23,C29 |
| 1 uF | 0603B105K160CT / C108463 | 0603 | C20 |
| 10 uF | CL21A106KPFNNNE / C17024 | 0805 | C5,C8,C28 |
| 22 uF | CL21A226MAQNNNE / C45783 | 0805 | C30,C31 |
| 22 ohm | 0603WAF220JT5E / C23345 | 0603 | R27,R28 |
| 330 ohm | 0603WAF3300T5E / C23138 | 0603 | R11,R18,R20 |
| 4.7 kohm | 0603WAF4701T5E / C23162 | 0603 | R17,R21 |
| 10 kohm | 0603WAF1002T5E / C25804 | 0603 | R1,R8,R9,R12-R16,R22-R24,R34,R36 |
| 47 kohm | 0603WAF4702T5E / C25819 | 0603 | R19 |
| 100 kohm | 0603WAF1003T5E / C25803 | 0603 | R35 |

Los restantes SMD ya conservaban MPN/LCSC validos en el esquema. `R2` y `R3`
mantienen huella 0603 pero no se incluyen como linea de compra hasta definir su
valor electrico.

## Conectores THT manuales

| Referencias | Huella | Uso |
|---|---|---|
| J1,J9,J10 | Header vertical 1x06 P2.54 mm | Debug y cargas. |
| J2,J12,J13,J14 | Header vertical 1x04 P2.54 mm | I2C y sensores. |
| J4,J15,J17,J18 | Header vertical 1x03 P2.54 mm | UART, RF y servos. |
| J5,J7,J8,J11,J19 | Header vertical 1x02 P2.54 mm | Entradas, sensores y 7 V. |
| J6 | Header vertical 2x04 P2.54 mm | BTS7960. |

Todos estan anotados como `Compra manual`; excluirlos de BOM y CPL de JLCPCB.

## Verificacion mecanica pendiente

- Mantener el keep-out de antena de U8 libre de cobre, vias, pistas y metal.
- Colocar D2/D5 antes de las pistas USB y adyacentes a J3/J16.
- Colocar C28, C30/C31 y L2 segun el loop corto VIN-SW-L-COUT de U9.
- Revisar la corriente admisible de J19, J17, J18 y sus pistas antes de usar
  servos con picos cercanos a 5 A.
